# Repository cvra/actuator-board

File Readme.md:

## CVRA Actuator Board

__Features:__

- STM32F302K8U6 (64K Flash, 16K RAM)
- IOs
    - 1 Digital input
    - 2 Analog input
    - 2 Servo PWM
    - 2 motor outputs for vacuum pump
- CAN interface with two 4pin Molex PicoBlade for daisy chaining
- Debug connector (7pin Molex PicoBlade)
    - SWD
    - UART

## Generating Digikey BOM using Kicost

Generate the Bom in XML format from KiCAD, then:

```
kicost -i actuator-board.xml --include digikey
```

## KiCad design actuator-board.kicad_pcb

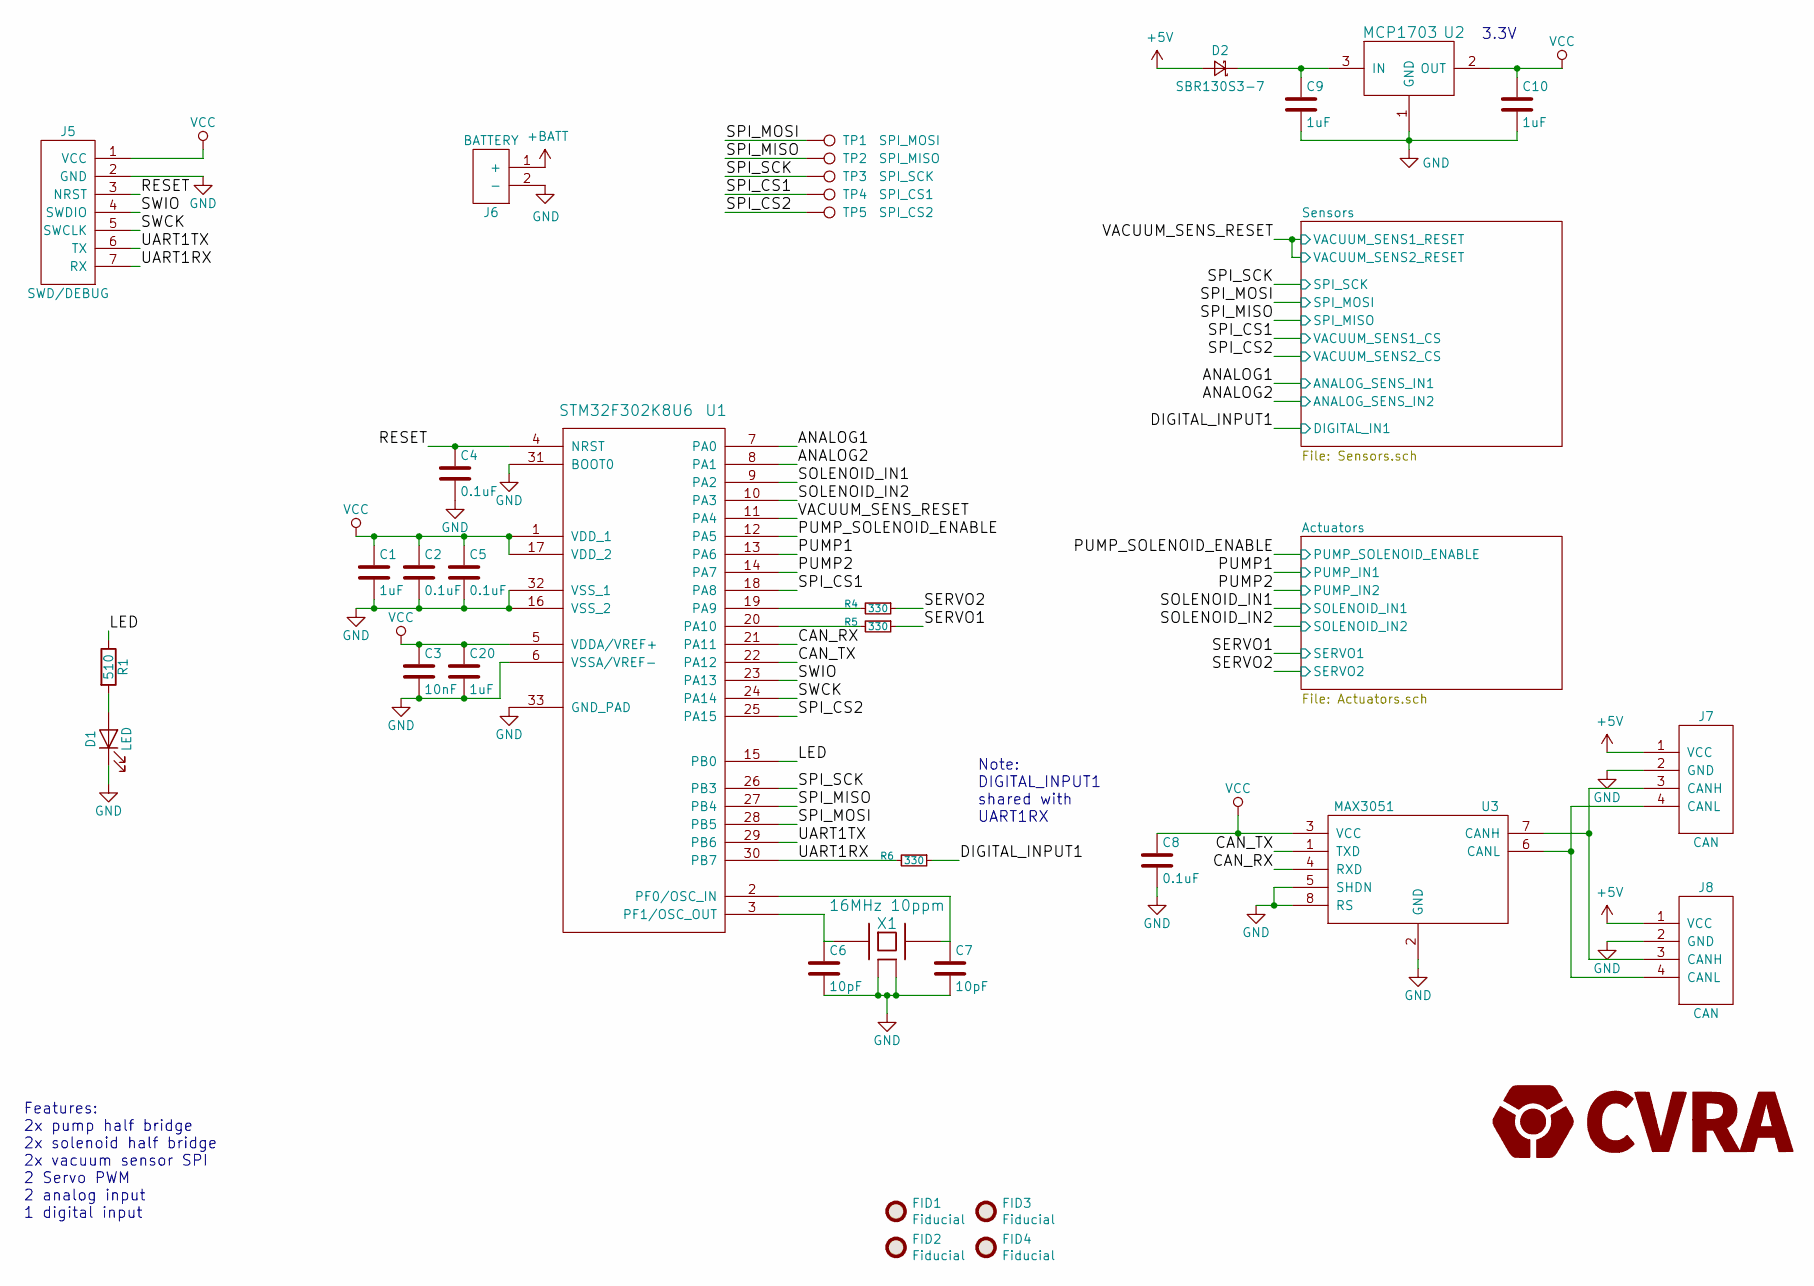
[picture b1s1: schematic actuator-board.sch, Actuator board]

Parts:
C1, C9, C10, C20: 1uF; C_0603_1608Metric; digikey# 399-3118-1-ND
C2, C4, C5, C8: 0.1uF; C_0603_1608Metric; digikey# 399-1283-1-ND
C3: 10nF; C_0603_1608Metric; digikey# 399-1092-1-ND
C6, C7: 10pF; C_0603_1608Metric; digikey# 399-17563-1-ND
D1: LED; LED_0603_1608Metric; digikey# VLMTG1300-GS08CT-ND
D2: SBR130S3-7; D_SOD-323_HandSoldering; digikey# SBR130S3-7DICT-ND
FID1, FID2, FID3, FID4: Fiducial; Fiducial_0.5mm_Mask1mm
J5: SWD/DEBUG; Molex_PicoBlade_53047-0710_1x07_P1.25mm_Vertical
J6: BATTERY; PinHeader_1x02_P2.54mm_Vertical
J7, J8: CAN; Molex_PicoBlade_53261-0471_1x04-1MP_P1.25mm_Horizontal; digikey# WM7622CT-ND
R1: 510; R_0603_1608Metric; digikey# 311-510GRCT-ND
R4, R5, R6: 330; R_0603_1608Metric; digikey# 311-330HRCT-ND
TP1: SPI_MOSI; TestPoint_Pad_D1.0mm
TP2: SPI_MISO; TestPoint_Pad_D1.0mm
TP3: SPI_SCK; TestPoint_Pad_D1.0mm
TP4: SPI_CS1; TestPoint_Pad_D1.0mm
TP5: SPI_CS2; TestPoint_Pad_D1.0mm
U1: STM32F302K8U6; QFN-32-1EP_5x5mm_P0.5mm_EP3.45x3.45mm; digikey# 497-14700-ND
U2: MCP1703; SOT-23; digikey# MCP1703T-3302E/CBCT-ND
U3: MAX3051; SOT-23-8; digikey# MAX3051EKA+TCT-ND
X1: 16MHz 10ppm; Crystal_SMD_SeikoEpson_TSX3225-4Pin_3.2x2.5mm; digikey# SER4069CT-ND

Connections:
+5V: D2.2 (A), J7.1 (VCC), J8.1 (VCC)
+BATT: J6.1 (+); also elsewhere on the board
/ANALOG1: U1.7 (PA0); also elsewhere on the board
/ANALOG2: U1.8 (PA1); also elsewhere on the board
/CAN_RX: U1.21 (PA11), U3.4 (RXD)
/CAN_TX: U1.22 (PA12), U3.1 (TXD)
/DIGITAL_INPUT1: R6.1; also elsewhere on the board
/LED: R1.1, U1.15 (PB0)
/PUMP1: U1.13 (PA6); also elsewhere on the board
/PUMP2: U1.14 (PA7); also elsewhere on the board
/PUMP_SOLENOID_ENABLE: U1.12 (PA5); also elsewhere on the board
/RESET: C4.1, J5.3 (NRST), U1.4 (NRST)
/SERVO1: R5.1; also elsewhere on the board
/SERVO2: R4.1; also elsewhere on the board
/SOLENOID_IN1: U1.9 (PA2); also elsewhere on the board
/SOLENOID_IN2: U1.10 (PA3); also elsewhere on the board
/SPI_CS1: TP4.1, U1.18 (PA8); also elsewhere on the board
/SPI_CS2: TP5.1, U1.25 (PA15); also elsewhere on the board
/SPI_MISO: TP2.1, U1.27 (PB4); also elsewhere on the board
/SPI_MOSI: TP1.1, U1.28 (PB5); also elsewhere on the board
/SPI_SCK: TP3.1, U1.26 (PB3); also elsewhere on the board
/SWCK: J5.5 (SWCLK), U1.24 (PA14)
/SWIO: J5.4 (SWDIO), U1.23 (PA13)
/UART1RX: J5.7 (RX), R6.2, U1.30 (PB7)
/UART1TX: J5.6 (TX), U1.29 (PB6)
/VACUUM_SENS_RESET: U1.11 (PA4); also elsewhere on the board
GND: C1.2, C2.2, C3.2, C4.2, C5.2, C6.2, C7.2, C8.2, C9.2, C10.2, C20.2, D1.1 (K), J5.2 (GND), J6.2 (-), J7.2 (GND), J8.2 (GND), U1.6 (VSSA/VREF-), U1.16 (VSS_2), U1.31 (BOOT0), U1.32 (VSS_1), U1.33 (GND_PAD), U2.1 (GND), U3.2 (GND), U3.5 (SHDN), U3.8 (RS), X1.2 (case), X1.4 (case); also elsewhere on the board
unnamed: C6.1, U1.3 (PF1/OSC_OUT), X1.1
unnamed: C7.1, U1.2 (PF0/OSC_IN), X1.3
unnamed: C9.1, D2.1 (K), U2.3 (IN)
unnamed: D1.2 (A), R1.2
unnamed: J7.3 (CANH), J8.3 (CANH), U3.7 (CANH)
unnamed: J7.4 (CANL), J8.4 (CANL), U3.6 (CANL)
unnamed: R4.2, U1.19 (PA9)
unnamed: R5.2, U1.20 (PA10)
VCC: C1.1, C2.1, C3.1, C5.1, C8.1, C10.1, C20.1, J5.1 (VCC), U1.1 (VDD_1), U1.5 (VDDA/VREF+), U1.17 (VDD_2), U2.2 (OUT), U3.3 (VCC); also elsewhere on the board

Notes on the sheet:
Features: 2x pump half bridge 2x solenoid half bridge 2x vacuum sensor SPI 2 Servo PWM 2 analog input 1 digital input
3.3V
Note: DIGITAL_INPUT1 shared with UART1RX

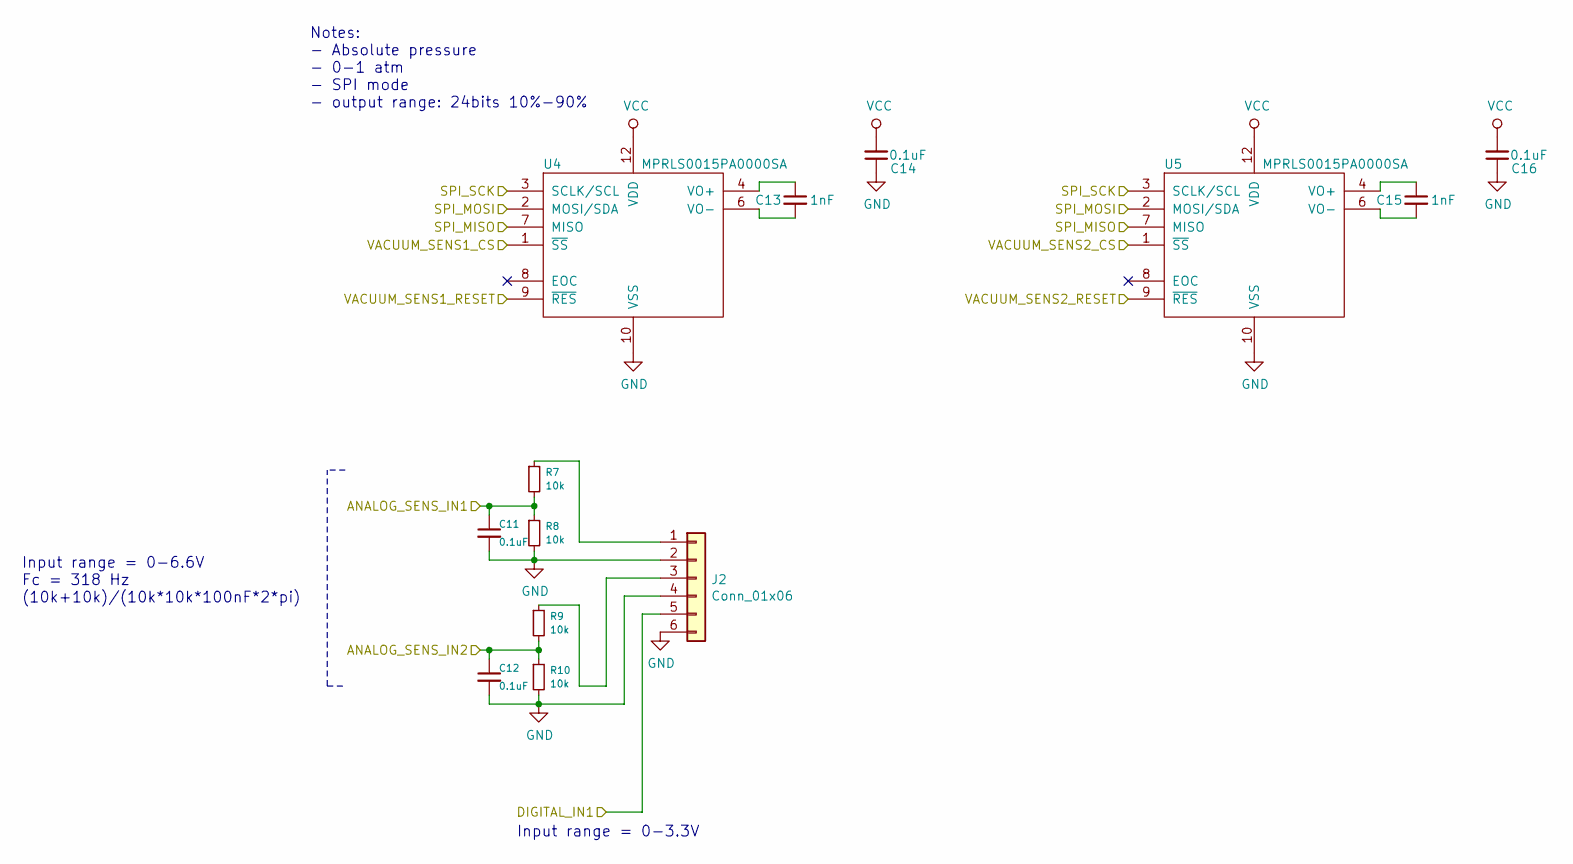
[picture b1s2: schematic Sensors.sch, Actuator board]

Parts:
C11, C12, C14, C16: 0.1uF; C_0603_1608Metric; digikey# 399-1283-1-ND
C13, C15: 1nF; C_0603_1608Metric; digikey# 399-8984-1-ND
J2: Conn_01x06; Molex_PicoBlade_53261-0671_1x06-1MP_P1.25mm_Horizontal; digikey# WM7626CT-ND
R7, R8, R9, R10: 10k; R_0603_1608Metric; digikey# 311-10KGRCT-ND
U4, U5: MPRLS0015PA0000SA; MPR-AbsoluteRef; digikey# 480-7099-1-ND

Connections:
/ANALOG1: C11.1, R7.2, R8.1; also elsewhere on the board
/ANALOG2: C12.1, R9.2, R10.1; also elsewhere on the board
/DIGITAL_INPUT1: J2.5; also elsewhere on the board
/SPI_CS1: U4.1 (~SS); also elsewhere on the board
/SPI_CS2: U5.1 (~SS); also elsewhere on the board
/SPI_MISO: U4.7 (MISO), U5.7 (MISO); also elsewhere on the board
/SPI_MOSI: U4.2 (MOSI/SDA), U5.2 (MOSI/SDA); also elsewhere on the board
/SPI_SCK: U4.3 (SCLK/SCL), U5.3 (SCLK/SCL); also elsewhere on the board
/VACUUM_SENS_RESET: U4.9 (~RES), U5.9 (~RES); also elsewhere on the board
GND: C11.2, C12.2, C14.1, C16.1, J2.2, J2.4, J2.6, R8.2, R10.2, U4.10 (VSS), U5.10 (VSS); also elsewhere on the board
unnamed: C13.1, U4.4 (VO+)
unnamed: C13.2, U4.6 (VO-)
unnamed: C15.1, U5.4 (VO+)
unnamed: C15.2, U5.6 (VO-)
unnamed: J2.1, R7.1
unnamed: J2.3, R9.1
VCC: C14.2, C16.2, U4.12 (VDD), U5.12 (VDD); also elsewhere on the board

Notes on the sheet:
Notes: - Absolute pressure - 0-1 atm - SPI mode - output range: 24bits 10%-90%
Input range = 0-6.6V Fc = 318 Hz (10k+10k)/(10k*10k*100nF*2*pi)
Input range = 0-3.3V

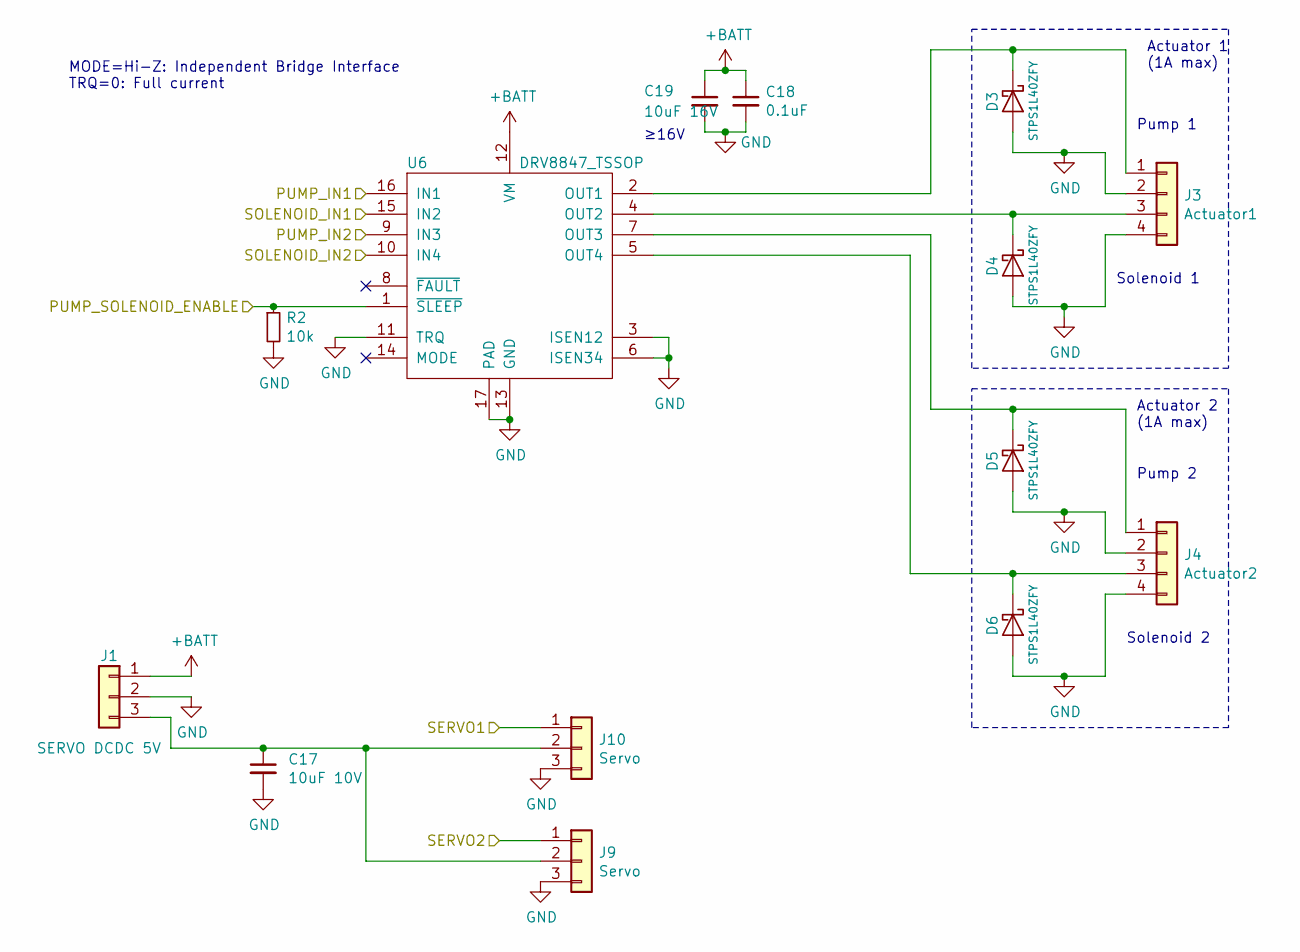
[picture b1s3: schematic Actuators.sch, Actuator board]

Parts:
C17: 10uF 10V; C_1206_3216Metric; digikey# 399-8155-1-ND
C18: 0.1uF; C_0603_1608Metric; digikey# 399-1283-1-ND
C19: 10uF 16V; C_1206_3216Metric; digikey# 399-7442-1-ND
D3, D4, D5, D6: STPS1L40ZFY; D_SOD-123F; digikey# 497-17153-1-ND
J1: SERVO DCDC 5V; PinHeader_1x03_P2.54mm_Vertical
J3: Actuator1; Molex_PicoBlade_53261-0471_1x04-1MP_P1.25mm_Horizontal; digikey# WM7622CT-ND
J4: Actuator2; Molex_PicoBlade_53261-0471_1x04-1MP_P1.25mm_Horizontal; digikey# WM7622CT-ND
J9, J10: Servo; Molex_PicoBlade_53261-0371_1x03-1MP_P1.25mm_Horizontal; digikey# WM7621CT-ND
R2: 10k; R_0603_1608Metric; digikey# 311-10KGRCT-ND
U6: DRV8847_TSSOP; TSSOP-16-1EP_4.4x5mm_P0.65mm; digikey# 296-53424-1-ND

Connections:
+BATT: C18.1, C19.1, J1.1, U6.12 (VM); also elsewhere on the board
/PUMP1: U6.16 (IN1); also elsewhere on the board
/PUMP2: U6.9 (IN3); also elsewhere on the board
/PUMP_SOLENOID_ENABLE: R2.1, U6.1 (~SLEEP); also elsewhere on the board
/SERVO1: J10.1; also elsewhere on the board
/SERVO2: J9.1; also elsewhere on the board
/SOLENOID_IN1: U6.15 (IN2); also elsewhere on the board
/SOLENOID_IN2: U6.10 (IN4); also elsewhere on the board
GND: C17.2, C18.2, C19.2, D3.2 (A), D4.2 (A), D5.2 (A), D6.2 (A), J1.2, J3.2, J3.4, J4.2, J4.4, J9.3, J10.3, R2.2, U6.3 (ISEN12), U6.6 (ISEN34), U6.11 (TRQ), U6.13 (GND), U6.17 (PAD); also elsewhere on the board
unnamed: C17.1, J1.3, J9.2, J10.2
unnamed: D3.1 (K), J3.1, U6.2 (OUT1)
unnamed: D4.1 (K), J3.3, U6.4 (OUT2)
unnamed: D5.1 (K), J4.1, U6.7 (OUT3)
unnamed: D6.1 (K), J4.3, U6.5 (OUT4)

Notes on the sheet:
Actuator 1 (1A max)
Actuator 2 (1A max)
MODE=Hi-Z: Independent Bridge Interface TRQ=0: Full current
≥16V
Pump 2
Solenoid 2
Solenoid 1
Pump 1

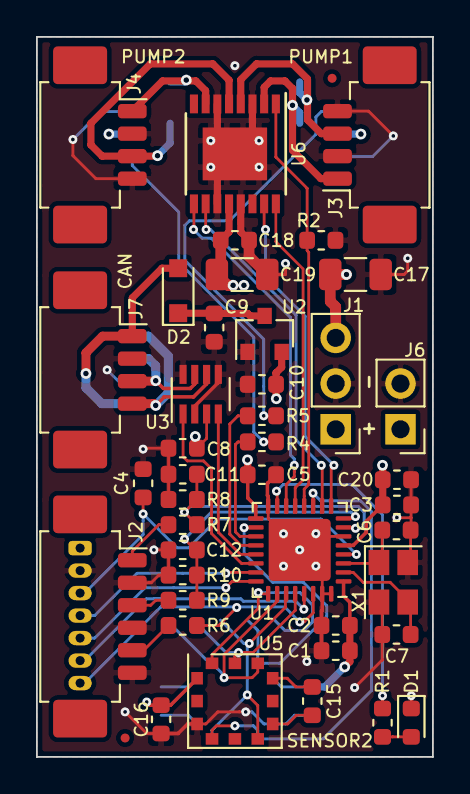
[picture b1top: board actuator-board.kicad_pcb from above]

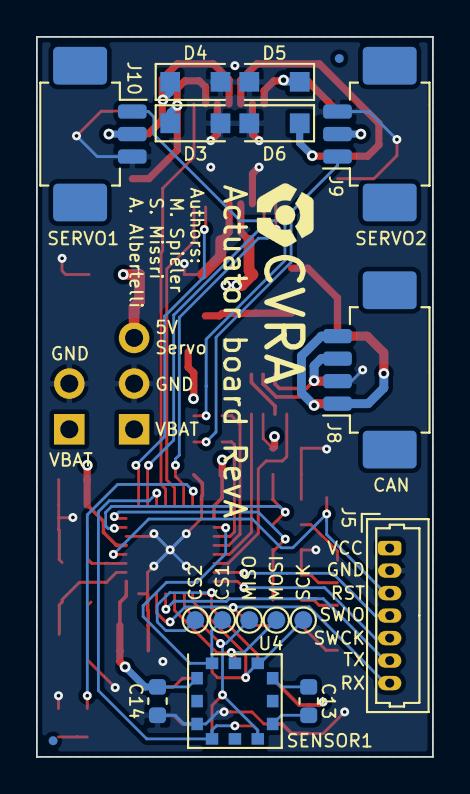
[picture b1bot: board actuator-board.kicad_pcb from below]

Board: 4 copper layers, 22.0 x 40.0 mm, 62 parts (19 on the bottom side), 47 nets.

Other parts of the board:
G1: LOGO; CVRA-logo-small

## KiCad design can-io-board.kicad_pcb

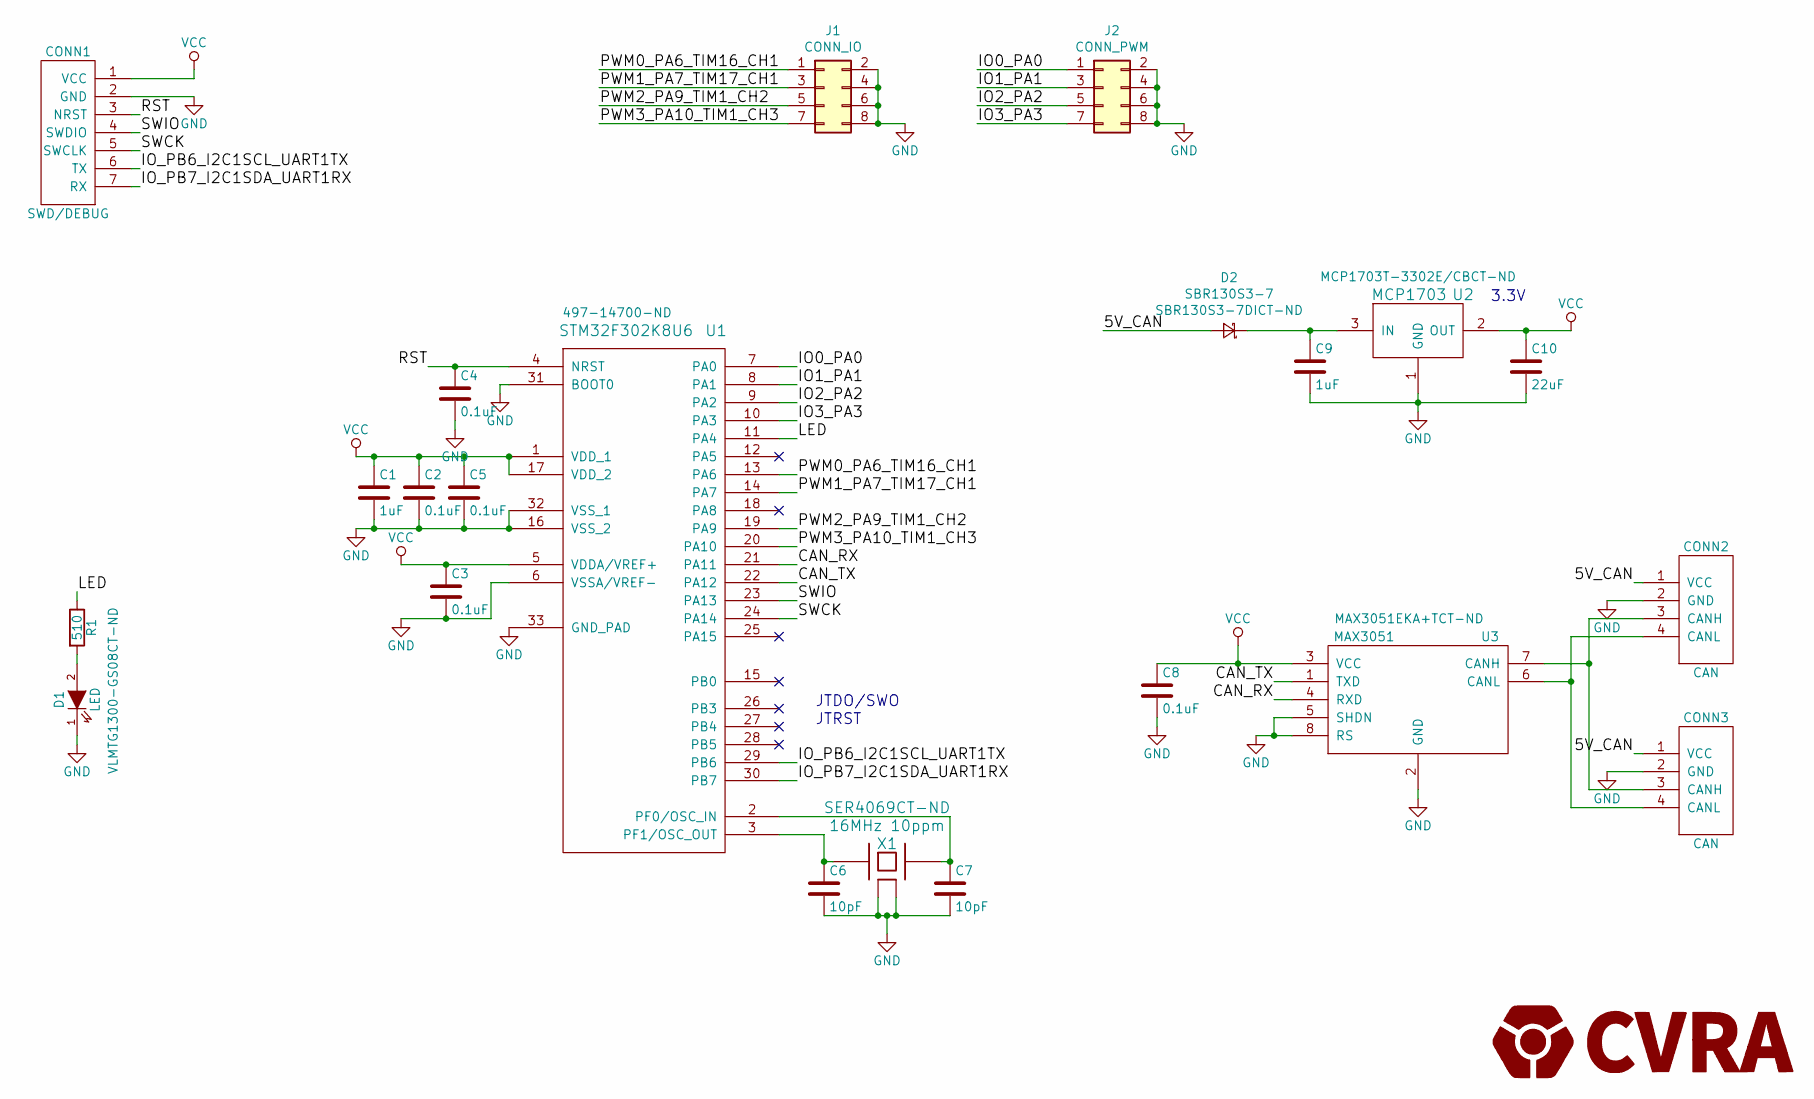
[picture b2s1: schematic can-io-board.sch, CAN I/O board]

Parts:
C1, C9: 1uF; C_0603_1608Metric
C2, C3, C4, C5, C8: 0.1uF; C_0402_1005Metric
C6, C7: 10pF; C_0402_1005Metric
C10: 22uF; C_0603_1608Metric
CONN1: SWD/DEBUG; Molex_PicoBlade_53048-1410_1x07_P1.25mm_Horizontal
CONN2, CONN3: CAN; Molex_PicoBlade_53261-0471_1x04-1MP_P1.25mm_Horizontal
D1: LED; LED_0603_1608Metric; Digikey VLMTG1300-GS08CT-ND
D2: SBR130S3-7; D_SOD-323_HandSoldering; Digikey SBR130S3-7DICT-ND
J1: CONN_IO; Molex_PicoBlade_53261-0871_1x08-1MP_P1.25mm_Horizontal
J2: CONN_PWM; Molex_PicoBlade_53261-0871_1x08-1MP_P1.25mm_Horizontal
R1: 510; R_0402_1005Metric
U1: STM32F302K8U6; QFN-32-1EP_5x5mm_Pitch0.5mm; Digikey 497-14700-ND
U2: MCP1703; _MCP1703-SOT-23A; Digikey MCP1703T-3302E/CBCT-ND
U3: MAX3051; _SOT23-8; Digikey MAX3051EKA+TCT-ND
X1: 16MHz 10ppm; Crystal_SMD_SeikoEpson_TSX3225-4Pin_3.2x2.5mm; Digikey SER4069CT-ND

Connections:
/5V_CAN: CONN2.1 (VCC), CONN3.1 (VCC), D2.2 (A)
/CAN_RX: U1.21 (PA11), U3.4 (RXD)
/CAN_TX: U1.22 (PA12), U3.1 (TXD)
/IO0_PA0: J2.1, U1.7 (PA0)
/IO1_PA1: J2.3, U1.8 (PA1)
/IO2_PA2: J2.5, U1.9 (PA2)
/IO3_PA3: J2.7, U1.10 (PA3)
/IO_PB6_I2C1SCL_UART1TX: CONN1.6 (TX), U1.29 (PB6)
/IO_PB7_I2C1SDA_UART1RX: CONN1.7 (RX), U1.30 (PB7)
/LED: R1.1, U1.11 (PA4)
/PWM0_PA6_TIM16_CH1: J1.1, U1.13 (PA6)
/PWM1_PA7_TIM17_CH1: J1.3, U1.14 (PA7)
/PWM2_PA9_TIM1_CH2: J1.5, U1.19 (PA9)
/PWM3_PA10_TIM1_CH3: J1.7, U1.20 (PA10)
/RST: C4.1, CONN1.3 (NRST), U1.4 (NRST)
/SWCK: CONN1.5 (SWCLK), U1.24 (PA14)
/SWIO: CONN1.4 (SWDIO), U1.23 (PA13)
GND: C1.2, C2.2, C3.2, C4.2, C5.2, C6.2, C7.2, C8.2, C9.2, C10.2, CONN1.2 (GND), CONN2.2 (GND), CONN3.2 (GND), D1.1 (K), J1.2, J1.4, J1.6, J1.8, J2.2, J2.4, J2.6, J2.8, U1.6 (VSSA/VREF-), U1.16 (VSS_2), U1.31 (BOOT0), U1.32 (VSS_1), U1.33 (GND_PAD), U2.1 (GND), U3.2 (GND), U3.5 (SHDN), U3.8 (RS), X1.2 (case), X1.4 (case)
unnamed: C6.1, U1.3 (PF1/OSC_OUT), X1.1
unnamed: C7.1, U1.2 (PF0/OSC_IN), X1.3
unnamed: C9.1, D2.1 (K), U2.3 (IN)
unnamed: CONN2.3 (CANH), CONN3.3 (CANH), U3.7 (CANH)
unnamed: CONN2.4 (CANL), CONN3.4 (CANL), U3.6 (CANL)
unnamed: D1.2 (A), R1.2
VCC: C1.1, C2.1, C3.1, C5.1, C8.1, C10.1, CONN1.1 (VCC), U1.1 (VDD_1), U1.5 (VDDA/VREF+), U1.17 (VDD_2), U2.2 (OUT), U3.3 (VCC)

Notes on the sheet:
3.3V
JTRST
JTDO/SWO

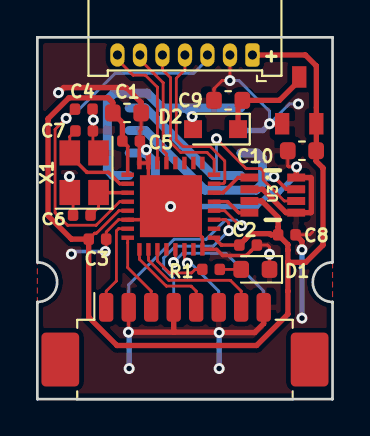
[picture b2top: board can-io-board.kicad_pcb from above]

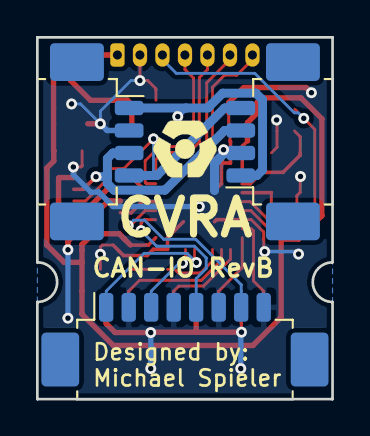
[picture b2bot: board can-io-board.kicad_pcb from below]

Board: 2 copper layers, 16.4 x 20.1 mm, 22 parts (3 on the bottom side), 25 nets.

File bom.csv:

Reference, Value, Footprint, Datasheet, Digikey,Quantity
U1,STM32F302K8U6,Housings_DFN_QFN:QFN-32-1EP_5x5mm_Pitch0.5mm,STM32F302K8U6,497-14700-ND,1
U2,MCP1703,MCP1703-SOT-23A,,MCP1703T-3302E/CBCT-ND,1
U3,MAX3051,SOT23-8,CAN Transceiver,MAX3051EKA+TCT-ND,1
X1,16MHz 10ppm,Crystal:Crystal_SMD_SeikoEpson_TSX3225-4Pin_3.2x2.5mm,TSX3225,SER4069CT-ND,1
D1,LED,LED_SMD:LED_0603_1608Metric,SMD 0603,VLMTG1300-GS08CT-ND,1
R1,510 Ohm,Resistor_SMD:R_0402_1005Metric,SMD 0402,311-510JRCT-ND,1
CONN1,SWD/DEBUG,Connector_Molex:Molex_PicoBlade_53048-1410_1x07_P1.25mm_Horizontal,53047-0710,WM1736-ND,1
"CONN2, CONN3",CAN,Connector_Molex:Molex_PicoBlade_53261-0471_1x04-1MP_P1.25mm_Horizontal,53261-0471,WM7622CT-ND,2
"J1, J2",CONN_IO,Connector_Molex:Molex_PicoBlade_53261-0871_1x08-1MP_P1.25mm_Horizontal,53261-0871,WM7626CT-ND,2
"C2,C3,C4,C5,C8",0.1uF,Capacitor_SMD:C_0402_1005Metric,SMD 0402,1276-1443-1-ND,5
"C1, C9",1uF,Capacitor_SMD:C_0603_1608Metric,SMD 0603,1276-1036-1-ND,2
C10,22uF,Capacitor_SMD:C_0603_1608Metric,SMD 0603,1276-1193-1-ND,1
"C6, C7",10pF,Capacitor_SMD:C_0402_1005Metric,SMD 0402,1276-1626-1-ND,2
D2,SBR130S3-7,Diode_SMD:D_SOD-323_HandSoldering,SOD-323,SBR130S3-7DICT-ND,1

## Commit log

2016-03-09 schematic & component placement
2016-03-09 add lib submodule
2016-03-09 pcb rules
2016-03-10 routing done
2016-03-10 add pdf schematic
2016-03-10 Set GND pad clearance and width
2016-03-10 Hide component references in silkscreen
2016-03-10 Improve VCC routing
2016-03-10 Flip debug connector
2016-03-10 nicer tracks
2016-03-10 Improve GND connection
2016-03-10 Remove silkscreen
2016-03-10 add gerber
2016-03-10 fix pin name, add silkscreen
2016-03-10 add final gerber
2016-03-10 add schemaic pdf
2016-03-10 track fp lib table
2016-03-10 optimize C9 connection
2016-03-11 add pcb preview
2016-03-11 add a readme
2016-03-27 oscillator reference
2018-10-17 Start layout on RevB
2018-10-17 CAN connector on opposite sides
2018-10-18 Reduced number of IO, use PicoBlade connector
2018-10-19 Routing almost finished
2018-10-19 fix DRC
2018-10-19 Capacitor spacing
2018-10-24 Improved GND connection, solder mask clearance
2018-10-25 Silkscreen placement
2018-10-25 Add Digikey ref in schematic, add BOM
2018-10-28 Add CAN reverse voltage protection diode
2018-10-28 Plot schematic, move RevA to subfolder
2018-10-28 Solder paste clearance -10%
2018-10-28 Gerber file export
2018-10-28 Add rendering image
2019-10-25 Start actuator-board
2019-10-25 remove CAN-IO stuff
2019-10-26 pin assignment WIP
2019-10-27 add doc
2020-01-18 Ignore kicad backups and PDFs
2020-01-18 Add components for half bridges and vaccuum sensor
2020-01-18 Finish the design of th actuator board schematic
2020-01-18 Add some design docs
2020-01-25 Correct schematics after review
2020-02-02 Cleanup labels, motor placement, power labels
2020-02-02 Change to Schottky flyback diode, update valve symbol
2020-02-02 Clear component annotation
2020-02-06 updated kicad lib symbols
2020-02-06 Switch to SPI, fixed sensor and motor driver symbols.
2020-02-08 Work on footprint assignment
2020-02-12 Review update
2020-02-12 Input range note, rough footprint assignment
2020-02-12 Create PCB file, import footprints, rough arrangement
2020-02-13 Upadate footprints, rough arrangement
2020-02-13 Add digikey references for BOM
2020-02-13 Rough component placement, defined outline
2020-02-16 Update footprints, better refdes, cleanup schematic, 40x22mm outline
2020-02-16 Update authors, DRC rules, layers, track/via settings
2020-02-20 Sensor/gpio/debug routing
2020-02-20 Refdes silkscreen text size 1mm -> 0.7mm
2020-02-22 layout: CAN, rearrange LED/CS1/CS2
2020-02-22 layout: power electronics, more components on F.Cu layer
2020-02-23 HTSSOP motor driver, component arrangment, added MCU capacitor
2020-02-23 Silk screen doc, ground vias, exchange servo 1 <-> 2
2020-03-01 Changes from review: move C2, move VCC via, add fiducials, component placement
2020-03-01 PDF schematic
2020-03-01 Gerber files
2020-03-08 Update DigiKey references
2020-03-08 Add pressure sensor 3D shape
2020-03-08 Update README and board rendering
2020-03-15 Fixed analog/digital input connector reference
